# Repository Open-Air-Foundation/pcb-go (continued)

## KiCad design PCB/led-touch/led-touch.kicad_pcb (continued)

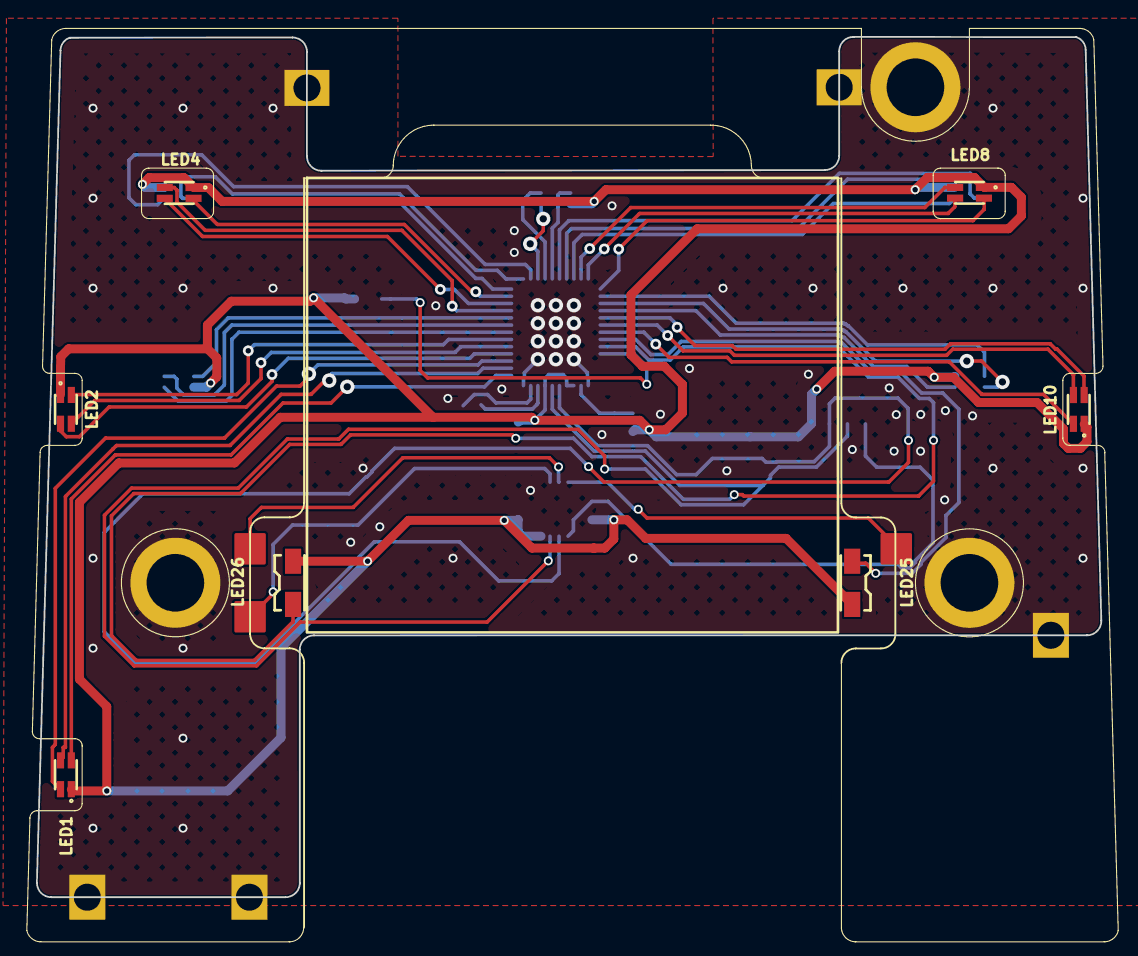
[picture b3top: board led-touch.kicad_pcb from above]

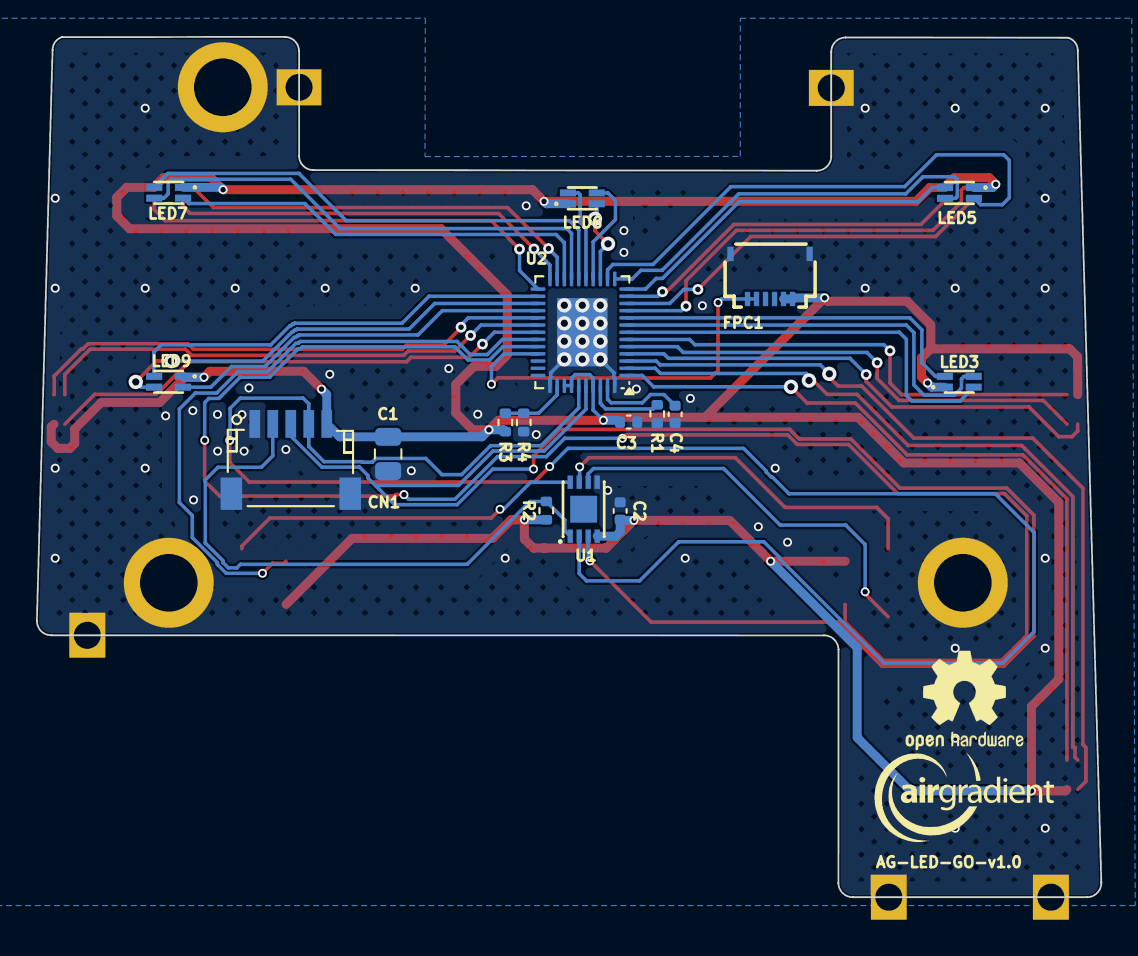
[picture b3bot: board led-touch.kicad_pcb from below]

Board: 2 copper layers, 59.1 x 47.8 mm, 26 parts (17 on the bottom side), 44 nets.

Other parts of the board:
EPAPER**: Epaper

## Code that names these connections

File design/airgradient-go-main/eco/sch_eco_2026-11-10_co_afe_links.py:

"""R-V3-17 links outside the CO SENSOR AFE block (drawn by sch_writer from blocks/co_afe.json):
U11 pins C/S/R get labels CO_CE/CO_S/CO_RE, U11 becomes ES1-CO-100-01 (same footprint, still DNP),
U17 P7 loses its NC flag and drives CO_MENB. Text-level edit, run once with the schematic closed."""
import re
import sys
import uuid

p = sys.argv[1]
t = open(p).read()
if '(label "CO_MENB"\n\t\t(at 247.65 191.77' in t:
    sys.exit("already applied")
U = lambda: str(uuid.uuid4())


def wire(a, b):
    return (f'\t(wire\n\t\t(pts\n\t\t\t(xy {a[0]} {a[1]}) (xy {b[0]} {b[1]})\n\t\t)\n\t\t(stroke\n'
            f'\t\t\t(width 0)\n\t\t\t(type default)\n\t\t)\n\t\t(uuid "{U()}")\n\t)\n')


def label(name, x, y, rot):
    j = "right bottom" if rot == 180 else "left bottom"
    return (f'\t(label "{name}"\n\t\t(at {x} {y} {rot})\n\t\t(effects\n\t\t\t(font\n\t\t\t\t(size 1.27 1.27)\n'
            f'\t\t\t)\n\t\t\t(justify {j})\n\t\t)\n\t\t(uuid "{U()}")\n\t)\n')


# U17 P7: drop the NC flag
m = re.search(r'\n\t\(no_connect\n\t\t\(at 236\.22 191\.77\)\n\t\t\(uuid "[^"]+"\)\n\t\)', t)
if not m:
    sys.exit("U17 P7 NC flag not found")
t = t[:m.start()] + t[m.end():]
new = [wire((236.22, 191.77), (247.65, 191.77)), label("CO_MENB", 247.65, 191.77, 0)]
# U11: R pin 1 (316.23), S pin 2 (320.04), C pin 3 (323.85), pins face left at x 321.31
for name, y in (("CO_RE", 316.23), ("CO_S", 320.04), ("CO_CE", 323.85)):
    new += [wire((321.31, y), (316.23, y)), label(name, 316.23, y, 180)]

# U11 fields
i = t.find('(property "Reference" "U11"')
s = t.rfind('\n\t(symbol\n', 0, i)
e = t.find('\n\t\t(instances', i)
blk = t[s:e]
nb = blk.replace('(property "Value" "PS1-CO-SMOKE-10k"', '(property "Value" "ES1-CO-100-01"')
nb = re.sub(r'\(property "Datasheet" "[^"]*"', '(property "Datasheet" "https://www.ecsense.com/"', nb)
nb = re.sub(r'\(property "Description" "[^"]*"',
            '(property "Description" "EC Sense 3-electrode CO sensor, 0 mV bias, 0-100 ppm; fitted by hand, PS1 footprint (R-V3-17)"', nb)
assert nb != blk and '"ES1-CO-100-01"' in nb
t = t[:s] + nb + t[e:]

k = t.rfind("\n\t(sheet_instances")
t = t[:k] + "\n" + "".join(new) + t[k:]
open(p, "w").write(t)
print("ok")

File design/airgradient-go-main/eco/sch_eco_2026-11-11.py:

"""Schematic ECO 2026-11-11 (R-V3-19, 20, 22, 23, 25), the hand-drawn parts of the sheet.
R-V3-19  R35 and R46 not fitted: U19 VIN1 comes off raw VBUS (LM66200 abs max 6 V), U8 runs from SYS only.
R-V3-20  C82 in series with C75 (BAT+ to PGND), so one shorted capacitor cannot short the cell.
R-V3-22  R26, R30 (I2C pull-ups) 10K to 100K.
R-V3-23  R49 (LP5036 IREF) 5.1K to 10K.
R-V3-25  R74, R75 499R in series with UART0: U4 TXD0/RXD0 become nets U0TXD/U0RXD.
The CO AFE change (R-V3-24) is drawn by sch_writer from blocks/co_afe.json.
Text-level edit, run once with the schematic closed in KiCad."""
import re
import sys
import uuid

path = sys.argv[1]
t = open(path).read()
ROOT = "/63bfc1c7-4623-455a-8f83-dca1d491c7db"
if '(reference "C82")' in t:
    sys.exit("already applied")

U = lambda: str(uuid.uuid4())


def prop(name, val, x, y, rot=0, hide=False):
    h = "\n\t\t\t(hide yes)" if hide else ""
    return (f'\t\t(property "{name}" "{val}"\n\t\t\t(at {x} {y} {rot}){h}\n\t\t\t(show_name no)\n'
            f'\t\t\t(do_not_autoplace no)\n\t\t\t(effects\n\t\t\t\t(font\n\t\t\t\t\t(size 1.27 1.27)\n'
            f'\t\t\t\t)\n\t\t\t)\n\t\t)\n')


def symbol(lib_id, ref, x, y, rot, props, mirror=None):
    m = f"\n\t\t(mirror {mirror})" if mirror else ""
    s = (f'\t(symbol\n\t\t(lib_id "{lib_id}")\n\t\t(at {x} {y} {rot}){m}\n\t\t(unit 1)\n\t\t(body_style 1)\n'
         f'\t\t(exclude_from_sim no)\n\t\t(in_bom yes)\n\t\t(on_board yes)\n\t\t(in_pos_files yes)\n'
         f'\t\t(dnp no)\n\t\t(uuid "{U()}")\n')
    s += "".join(props)
    for p in ("2", "1"):
        s += f'\t\t(pin "{p}"\n\t\t\t(uuid "{U()}")\n\t\t)\n'
    s += (f'\t\t(instances\n\t\t\t(project "airgradient-go-main"\n\t\t\t\t(path "{ROOT}"\n'
          f'\t\t\t\t\t(reference "{ref}")\n\t\t\t\t\t(unit 1)\n\t\t\t\t)\n\t\t\t)\n\t\t)\n\t)\n')
    return s


def wire(a, b):
    return (f'\t(wire\n\t\t(pts\n\t\t\t(xy {a[0]} {a[1]}) (xy {b[0]} {b[1]})\n\t\t)\n\t\t(stroke\n'
            f'\t\t\t(width 0)\n\t\t\t(type default)\n\t\t)\n\t\t(uuid "{U()}")\n\t)\n')


def label(name, x, y):
    return (f'\t(label "{name}"\n\t\t(at {x} {y} 0)\n\t\t(effects\n\t\t\t(font\n\t\t\t\t(size 1.27 1.27)\n'
            f'\t\t\t)\n\t\t\t(justify left bottom)\n\t\t)\n\t\t(uuid "{U()}")\n\t)\n')


def text(s, x, y):
    return (f'\t(text "{s}"\n\t\t(exclude_from_sim no)\n\t\t(at {x} {y} 0)\n\t\t(effects\n\t\t\t(font\n'
            f'\t\t\t\t(size 1.27 1.27)\n\t\t\t)\n\t\t\t(justify left top)\n\t\t)\n\t\t(uuid "{U()}")\n\t)\n')


def block(ref):
    """(start, end) of the symbol whose reference is ref."""
    i = t.find(f'(property "Reference" "{ref}"')
    if i < 0:
        sys.exit(f"{ref} not found")
    s = t.rfind('\n\t(symbol\n', 0, i)
    e = t.find('\n\t)\n', i) + 3
    return s, e


def edit(ref, fn):
    global t
    s, e = block(ref)
    new = fn(t[s:e])
    if new == t[s:e]:
        sys.exit(f"{ref}: nothing changed")
    t = t[:s] + new + t[e:]


def once(old, new):
    global t
    if t.count(old) != 1:
        sys.exit(f"expected one match, found {t.count(old)}: {old[:60]!r}")
    t = t.replace(old, new)


def set_prop(b, name, val):
    n = re.subn(rf'\(property "{name}" "[^"]*"', f'(property "{name}" "{val}"', b, count=1)
    if n[1] != 1:
        sys.exit(f"property {name} not found")
    return n[0]


def shift(b, dx, dy):
    """Move a symbol and its field texts."""
    def f(m):
        x, y = round(float(m.group(1)) + dx, 4), round(float(m.group(2)) + dy, 4)
        return f"(at {x:g} {y:g} {m.group(3)})"
    return re.sub(r'\(at (-?[\d.]+) (-?[\d.]+) (\d+)\)', f, b)


# R-V3-19: R35, R46 not fitted
for ref in ("R35", "R46"):
    edit(ref, lambda b: b.replace("(in_bom yes)", "(in_bom no)", 1).replace("(dnp no)", "(dnp yes)", 1))

# R-V3-22: I2C pull-ups 100K (same part as R61)
for ref in ("R26", "R30"):
    edit(ref, lambda b: set_prop(set_prop(set_prop(set_prop(
        b, "Value", "100K"),
        "Datasheet", "https://lcsc.com/product-detail/Chip-Resistor-Surface-Mount_100KR-1003-1_C60491.html"),
        "Description", "RC0402FR-07100KL"),
        "LCSC Part", "C60491"))
# "100K" is one character longer than "10K" and would reach R30: R26's texts go to its left side
edit("R26", lambda b: b.replace("(at 181.61 35.5599 0)", "(at 176.53 35.5599 0)", 1)
     .replace("(at 181.61 38.0999 0)", "(at 176.53 38.0999 0)", 1).replace("(justify right)", "(justify left)", 2))

# R-V3-23: LP5036 IREF 10K (same part as R36)
edit("R49", lambda b: set_prop(set_prop(set_prop(set_prop(
    b, "Value", "10K"),
    "Datasheet", "https://lcsc.com/product-detail/Others_Huaxin-S-T-MR04X1002FTL_C327797.html"),
    "Description", "MR04X1002FTL"),
    "LCSC Part", "C327797"))

# R-V3-20: C75 up 2.54, C82 beside it, the PGND symbol moves to C82
edit("C75", lambda b: shift(b, 0, -2.54))
edit("#PWR0121", lambda b: shift(b, 12.7, -1.27))
once("(xy 49.53 275.59) (xy 49.53 279.4)", "(xy 49.53 275.59) (xy 49.53 276.86)")
once("(xy 49.53 287.02) (xy 49.53 288.29)", "(xy 49.53 284.48) (xy 49.53 285.75)")
C100072 = ("https://lcsc.com/product-detail/Multilayer-Ceramic-Capacitors-MLCC-SMD-SMT_SAMSUNG_"
           "CL05A104KA5NNNC_100nF-104-10-25V_C100072.html")
new = [wire((49.53, 285.75), (52.07, 285.75)),
       symbol("Device:C", "C82", 55.88, 285.75, 90, [
           prop("Reference", "C82", 55.88, 289.56, 90),
           prop("Value", "0.1uF/25V", 55.88, 292.1, 90),
           prop("Footprint", "Capacitor_SMD:C_0402_1005Metric", 55.88, 285.75, hide=True),
           prop("Datasheet", C100072, 55.88, 285.75, hide=True),
           prop("Description", "CL05A104KA5NNNC", 55.88, 285.75, hide=True),
           prop("LCSC Part", "C100072", 55.88, 285.75, hide=True),
           prop("LCSC", "", 55.88, 285.75, hide=True),
       ]),
       wire((59.69, 285.75), (62.23, 285.75)), wire((62.23, 285.75), (62.23, 287.02))]

# R-V3-25: UART0 series resistors, drawn like the SPI series group
once('(label "MCU_TX"\n\t\t(at 172.72 58.42 180)', '(label "U0TXD"\n\t\t(at 172.72 58.42 180)')
once('(label "MCU_RX"\n\t\t(at 172.72 60.96 180)', '(label "U0RXD"\n\t\t(at 172.72 60.96 180)')
for ref, y, left, right in (("R74", 60.96, "U0TXD", "MCU_TX"), ("R75", 68.58, "MCU_RX", "U0RXD")):
    new += [label(left, 226.06, y), wire((226.06, y), (236.22, y)),
            symbol("Device:R", ref, 240.03, y, 90, [
                prop("Reference", ref, 240.03, round(y + 2.794, 3), 90),
                prop("Value", "499R", 240.03, round(y + 5.334, 3), 90),
                prop("Footprint", "Resistor_SMD:R_0402_1005Metric", 240.03, y, hide=True),
                prop("Datasheet", "https://www.lcsc.com/product-detail/C2960788.html", 240.03, y, hide=True),
                prop("Description", "FRC0402F4990TS", 240.03, y, hide=True),
                prop("LCSC Part", "C2960788", 240.03, y, hide=True),
                prop("LCSC", "", 240.03, y, hide=True),
            ], mirror="x"),
            wire((243.84, y), (247.65, y)), label(right, 247.65, y)]
new.append(text("R74/R75 499R (R-V3-25):\\nEspressif asks it on U0TXD;\\nR75 lets a tool drive RX0.", 226.06, 50.8))
new.append(text("R35, R46 DNP (R-V3-19):\\nU19 VIN1 off raw VBUS\\n(6 V abs max), SYS only", 233.68, 315.595))

i = t.rfind("\n\t(sheet_instances")
if i < 0:
    sys.exit("sheet_instances not found")
t = t[:i] + "\n" + "".join(new) + t[i:]
open(path, "w").write(t)
print("ok")

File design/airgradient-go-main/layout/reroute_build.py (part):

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
    # -- U5 pins that face the F.Cu power wall ---------------------------------------------------
    g = "u5-escapes"
    s.group(g, "U5 pins behind the F.Cu power wall. QON crosses the BAT+ strap through the F.Cu gap between REGN and C22. CHG_INT cannot "
               "get south on F or B (TS, TS_BIAS and the SYS and Pack+ pours), so it runs on In2 beside SDA and SCL, as v3 did on B.Cu "
               "round the west end before the NTC lanes took that way. U5-TS keeps its v3 ties and reaches the NTC lane on F.Cu along the battery cut-out.")
    s.t(g, "/QON", "F.Cu", 0.2, [(122.23, 99.43), (122.23, 100.37), (121.68, 100.92), (121.10, 100.92), (120.87, 100.69), (120.62, 100.69)])
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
